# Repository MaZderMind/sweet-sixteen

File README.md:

# Sweet Sixteen
> a 16x2 Characters Sixten-Segment, RaspberryPi driven Display

## Quick Links
 * <a href="Hardware/Schematic.pdf">Schematic (PDF)</a>
 * <a href="Hardware/PCB-Layout.png">PCB Layout (Image)</a>
 * <a href="Hardware/BOM.ods">BOM</a>
 * <a href="Datasheets/">Datasheets</a>
 * <a href="https://github.com/MaZderMind/sweet-sixteen-scheduler">Software</a>

## System Design

The System is built around [STP16CPC26](Datasheets/STP16CPC26.pdf) LED-Drivers in a direct drive configuration. Each LED-Driver has 16 Constant-Current sinks, each of which powers one Segment of the [PSA12-11](Datasheets/PSA12_11CGKWA.pdf) 16-Segment Displays.

The PCBs are built to be Chainable. The first Board in the Chain provides Data and the 5V Rail. It also carries the RaspberryPi "Piggy Back". The Board powers the Pi via its GPIO-Header, so there is no need to supply extra Power to the Pi (and you should not do that.)

## Signal Flow

The RaspberryPi generates Clock and Data via its Hardware-SPI Port (GPIO 10 & 11). Additionally it generates a Latch-Signal on GPIO 22 and an inverted Output-Enable Signal, which is can be used to Dim the LED-Drivers down, on one of its Hardware PWM Pins (GPIO 18).

All of these Signals are 3.3V rated. They are directly fed into a [SN74HCT08](Datasheets/sn74hct08.pdf) and-gate which is used to convert the Signals to 5V compatible swing. These Signal then go on a parallel bus to all LED-Drivers (Clock, Latch and Output-Enable) resp. to the first LED-Driver (Data).

The LED-Drivers behave like Shift-Registers on the Data-Side, so the Data-Line ist chained from the input of one LED-Driver to the next, through all 9 Drivers. Drivers 1-8 each control one of the 16 Segments of one of the 8 Digits, while the 9th Driver controls the Decimal Points of all Digits as well as the Row of the 8 LEDs on the bottom of the PCB.

The Data-Output of the last LED-Driver as well as the paralleld Bus of Clock, Latch and Output Enable are fed to another [SN74HCT08](Datasheets/sn74hct08.pdf) and-gate which is here used as a line-driver to drive the LED-Drivers on the next PCB. After the and-gate the Signal is routed to Solder-Pads on the edge of the PCB which line up with matching Pads on the opposite Edge of the next PCB.

The Signals coming from those Pads feed into the next 9 LED-Drivers, just as the Raspberry-Pi did on the first PCB. The Components needed to interface to the Raspberry-Pi (Connectors, Fuse, and-Gate and some Caps) are not fitted on the following PCBs.

## Power System

The Whole System is Powered from a Notebook-Plugpack. I chose a Dell 19V/90W Plugpack because they are quite easy to get new or used on ebay for a small amount of money everywhere on the world. I terms of Power per Euro/Dollar Notebook-Chargers are unbeatable.

The 19V (actually the Input-Rail can range from 15V to 40V DC) is fed into two DC-DC Converter Modules on the first PCB, each of which is capable of generating up to 3A.

The first DC-DC Converter generates 5V and powers the RaspberryPi as well as as all the Logic-ICs on all PCBs.
The second Converter generates a 4.4V rail used to Power the LEDs – but this time only on the first PCB.

The following PCBs accept the 5V VCC Rail generated on the first PCB as well as the input-voltage from the Plugpack, also via Pads on the Edge of the PCBs. They are only fitted with the second DC-DC Converter and generate their own 4.4V VLED Rail for their LEDS.

When all LEDs ar on, the System draws about 45W or a little more, so 60W Dell Charger should also be okay. Take a look at the [Power Calculations](Hardware/Power%20Calculations.ods) to learn how the Current is consumed and which Temperature-Rise is to expect from the LED-Drivers.

## Software

The Software that runs the Display, pulls down the latest tweets, shows what the canteen has for Lunch, Blinks when a Software-Build fails or when it's a colleagues birthday grows over on [MaZderMind/sweet-sixteen-scheduler](https://github.com/MaZderMind/sweet-sixteen-scheduler).

## Build one yourself

To build your own you need
 * some PCBs
 * some Parts
 * a RaspberryPi
 * time, patience and tools to solder the SMD-Components (which is totally doable by Hand vith a good soldering Iron)

For the PCBs you can use the [pre-generated Gerbers](Gerbers/) but *be aware* that these are the Gerbers for rev1. I fixed some Bugs in rev1 but my Display uses rev0 boards and I have *not ordered or testet* the rev1 PCBs, though I'm quite sure they will work. If you want to play save, you can Download the rev0 Gerbers from the [rev0 Release-Page](https://github.com/MaZderMind/sweet-sixteen/releases/tag/rev0).

On the other Hand you might want to design in another Power-Connector, if you don't want to use Dell Plugpacks. The Schematics and PCBs are made with [KiCad](http://kicad-pcb.org/) which is Free Software and available on all Operating Systems. For the Parts please take a look at the [BOM](Hardware/BOM.ods) which contains all Parts I used.

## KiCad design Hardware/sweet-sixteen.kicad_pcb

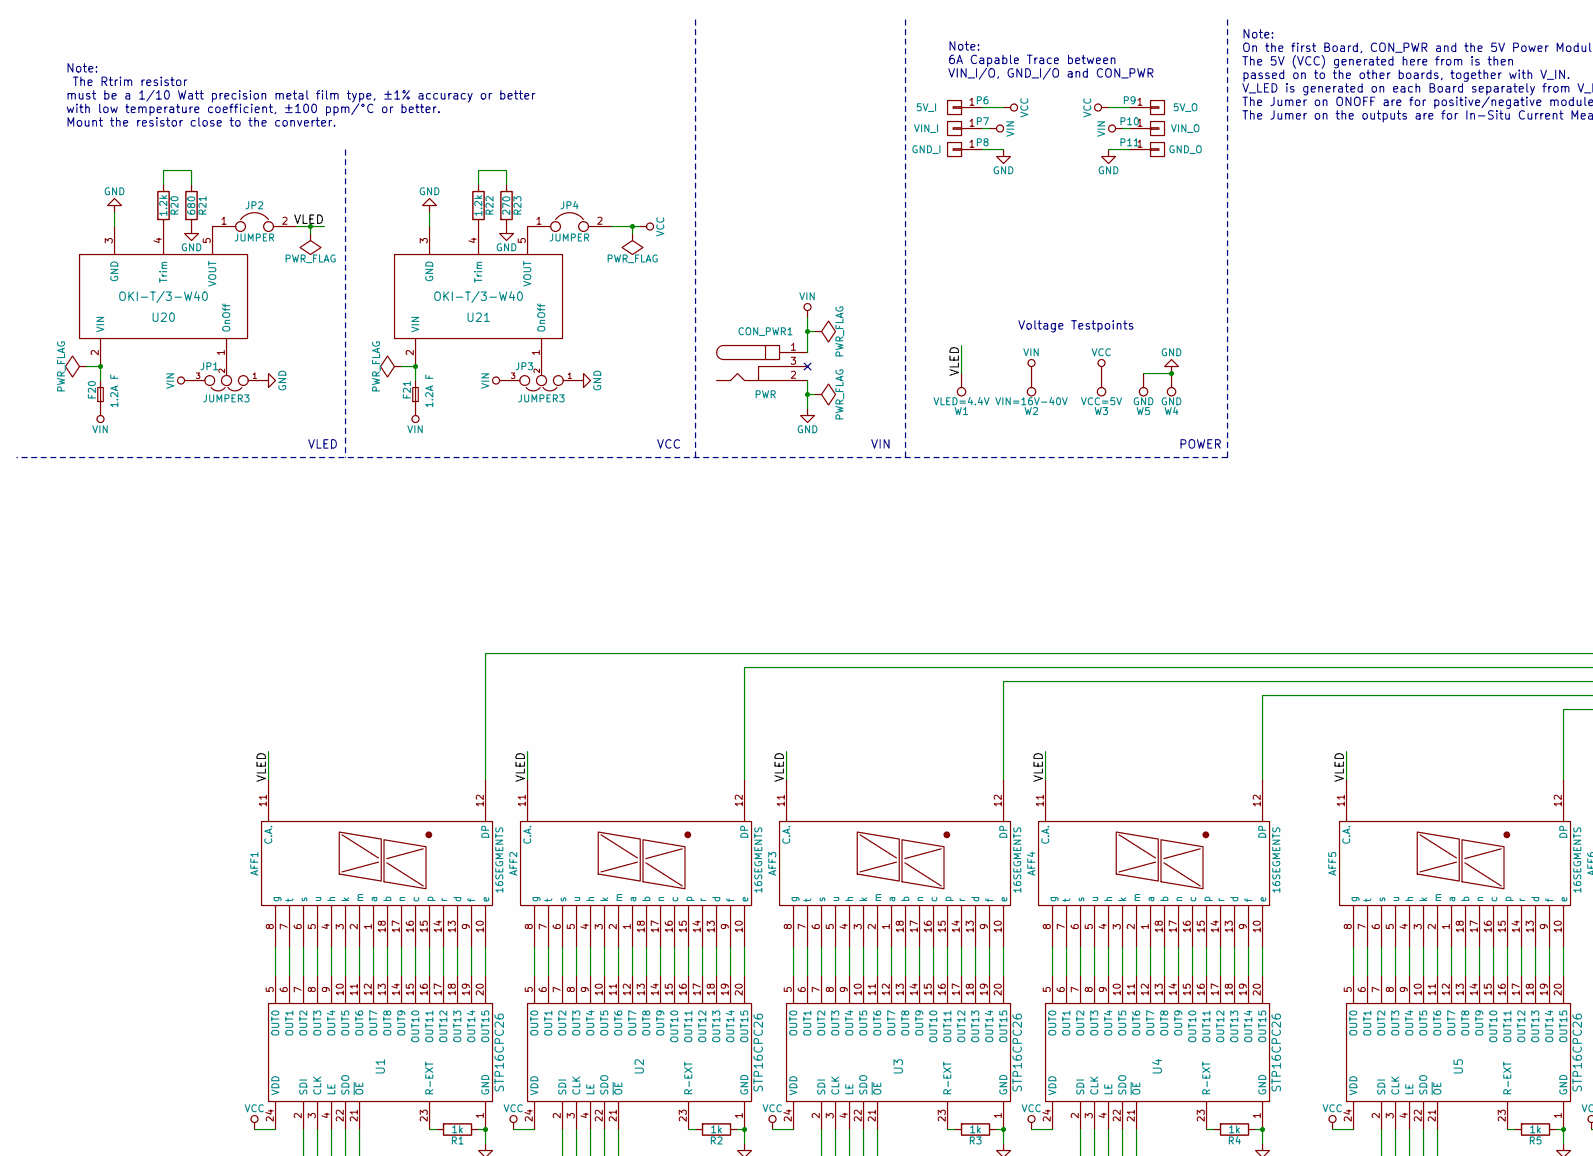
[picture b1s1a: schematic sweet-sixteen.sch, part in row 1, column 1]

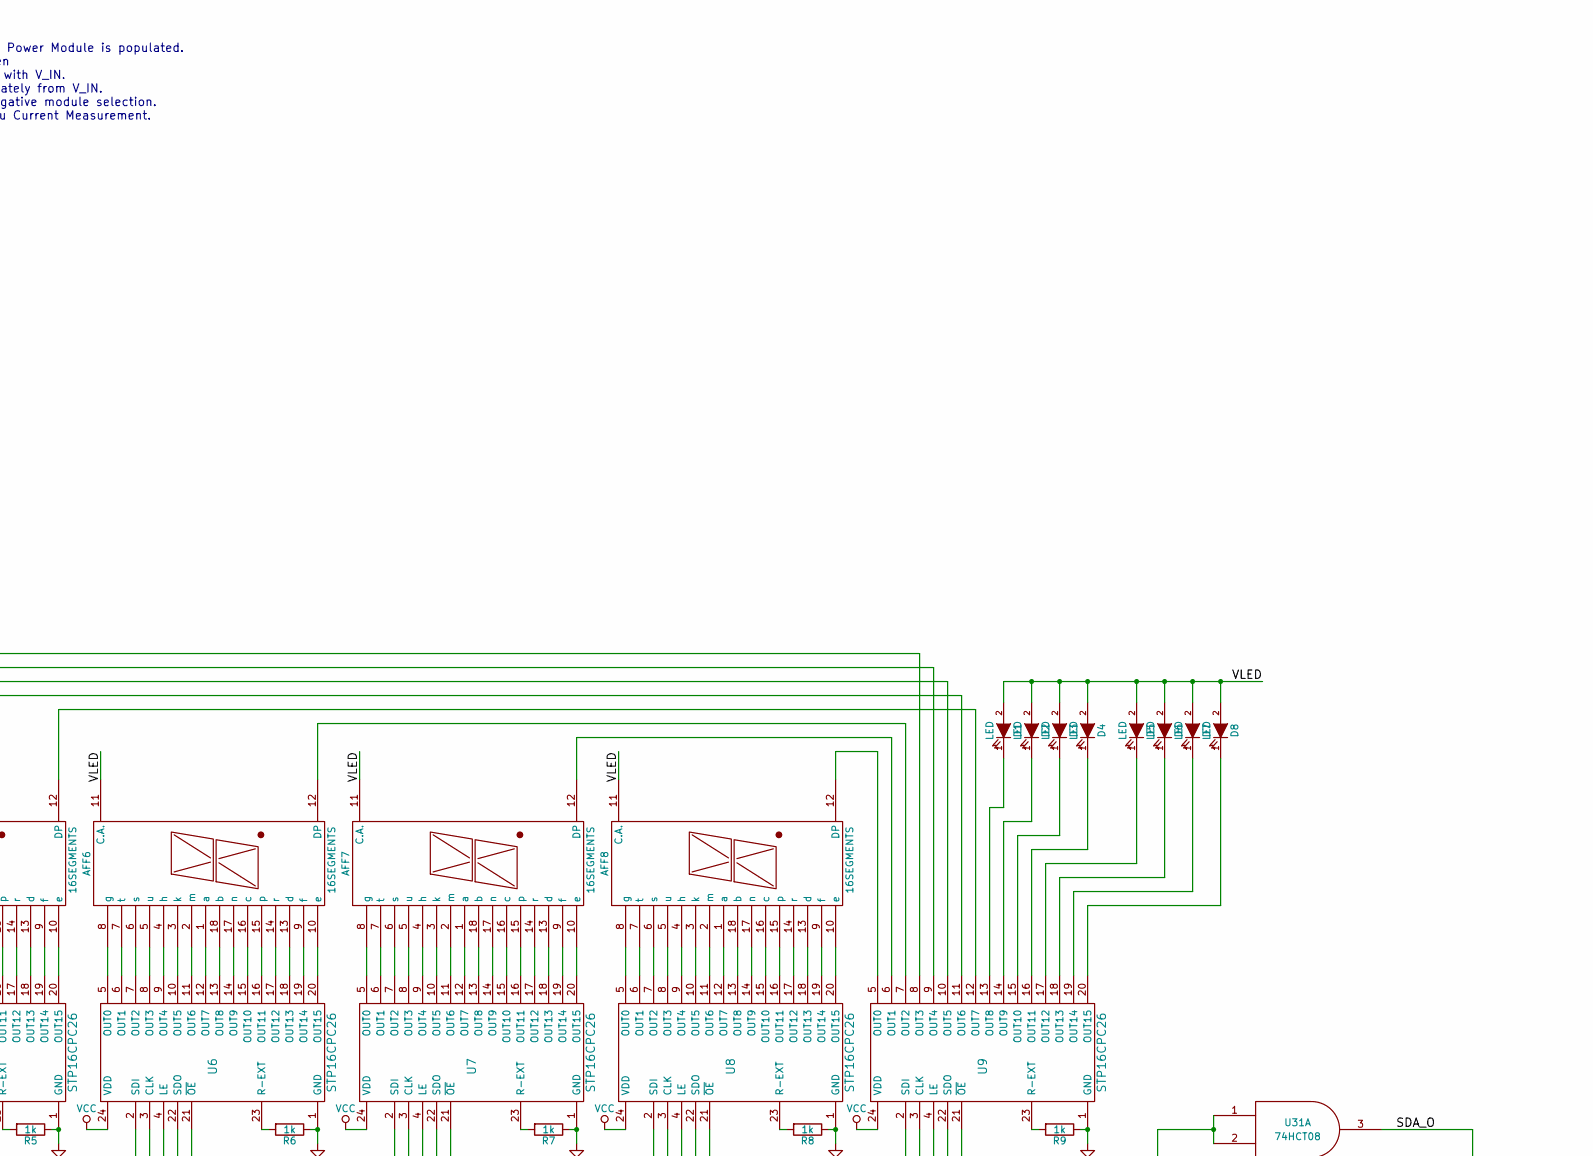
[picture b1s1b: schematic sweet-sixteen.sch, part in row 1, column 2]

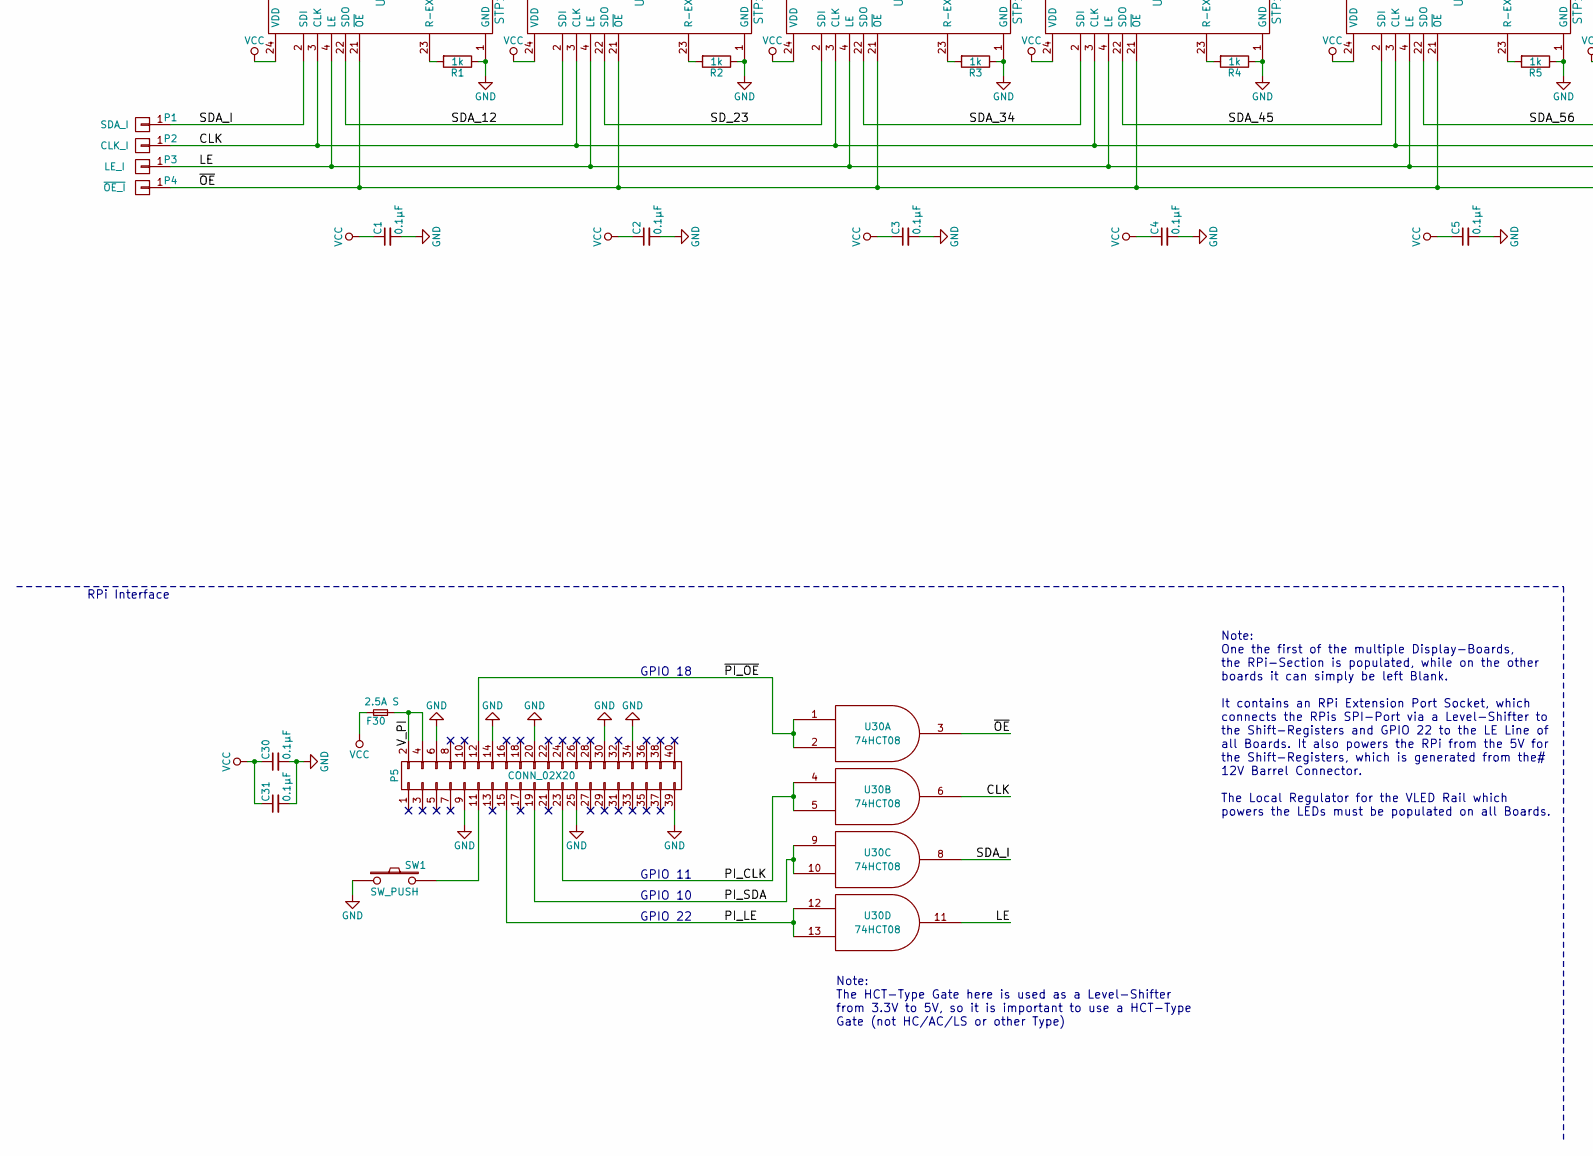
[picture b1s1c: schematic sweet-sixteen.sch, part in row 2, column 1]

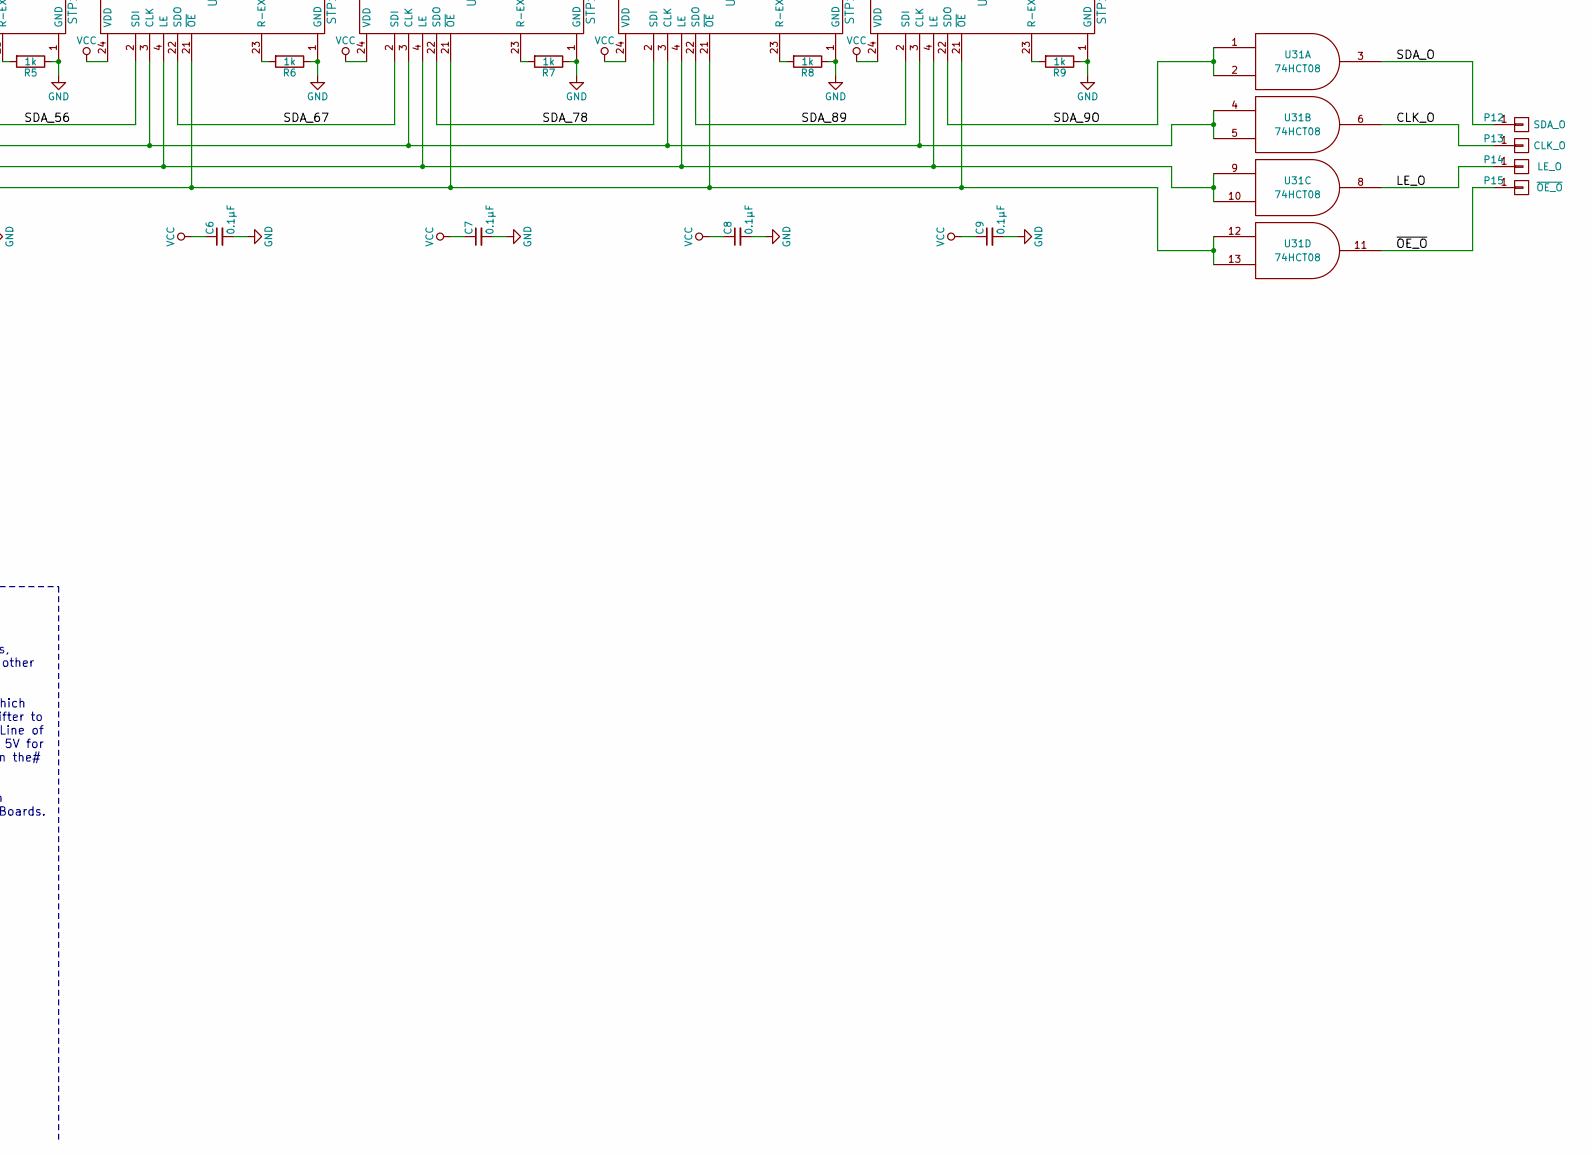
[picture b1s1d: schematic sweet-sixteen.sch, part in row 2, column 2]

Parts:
AFF1, AFF2, AFF3, AFF4, AFF5, AFF6, AFF7, AFF8: 16SEGMENTS; PSA12-11
C1, C2, C3, C4, C5, C6, C7, C8, C9, C30, C31: 0.1μF; C_0805_HandSoldering
CON_PWR1: PWR; DELL-PCON
D1, D2, D3, D4, D5, D6, D7, D8: LED; LED-5MM
F20, F21: 1.2A F; SMD-2112_Pol
F30: 2.5A S; SMD-2112_Pol
JP1, JP3: JUMPER3; SMD_Jumper_3
JP2, JP4: JUMPER; SMD_Jumper_2
P1: SDA_I; Measurement_Point_Square-SMD-Pad_Big
P2: CLK_I; Measurement_Point_Square-SMD-Pad_Big
P3: LE_I; Measurement_Point_Square-SMD-Pad_Big
P4: ~OE_I; Measurement_Point_Square-SMD-Pad_Big
P5: CONN_02X20; rpi-header
P6: 5V_I; Measurement_Point_Square-SMD-Pad_Big
P7: VIN_I; Measurement_Point_Square-SMD-Pad_Big
P8: GND_I; Measurement_Point_Square-SMD-Pad_Big
P9: 5V_O; Measurement_Point_Square-SMD-Pad_Big
P10: VIN_O; Measurement_Point_Square-SMD-Pad_Big
P11: GND_O; Measurement_Point_Square-SMD-Pad_Big
P12: SDA_O; Measurement_Point_Square-SMD-Pad_Big
P13: CLK_O; Measurement_Point_Square-SMD-Pad_Big
P14: LE_O; Measurement_Point_Square-SMD-Pad_Big
P15: ~OE_O; Measurement_Point_Square-SMD-Pad_Big
R1, R2, R3, R4, R5, R6, R7, R8, R9: 1k; R_1206_HandSoldering
R20, R22: 1.2k; R_1206_HandSoldering
R21: 680; R_1206_HandSoldering
R23: 270; R_1206_HandSoldering
SW1: SW_PUSH; ADTSM61
U1, U2, U3, U4, U5, U6, U7, U8, U9: STP16CPC26; STP16CPC26MTR
U20, U21: OKI-T/3-W40; OKI-T3
U30, U31: 74HCT08; SN74HCT08D
W1: VLED=4.4V; Measurement_Point_Round-SMD-Pad_Big
W2: VIN=16V-40V; Measurement_Point_Round-SMD-Pad_Big
W3: VCC=5V; Measurement_Point_Round-SMD-Pad_Big
W4, W5: GND; Measurement_Point_Round-SMD-Pad_Big

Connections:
/CLK: P2.1, U1.3 (CLK), U2.3 (CLK), U3.3 (CLK), U4.3 (CLK), U5.3 (CLK), U6.3 (CLK), U7.3 (CLK), U8.3 (CLK), U9.3 (CLK), U30.6, U31.4, U31.5
/CLK_O: P13.1, U31.6
/LE: P3.1, U1.4 (LE), U2.4 (LE), U3.4 (LE), U4.4 (LE), U5.4 (LE), U6.4 (LE), U7.4 (LE), U8.4 (LE), U9.4 (LE), U30.11, U31.9, U31.10
/LE_O: P14.1, U31.8
/PI_CLK: P5.23, U30.4, U30.5
/PI_LE: P5.15, U30.12, U30.13
/PI_SDA: P5.19, U30.9, U30.10
/SDA_9O: U9.22 (SDO), U31.1, U31.2
/SDA_12: U1.22 (SDO), U2.2 (SDI)
/SDA_34: U3.22 (SDO), U4.2 (SDI)
/SDA_45: U4.22 (SDO), U5.2 (SDI)
/SDA_56: U5.22 (SDO), U6.2 (SDI)
/SDA_67: U6.22 (SDO), U7.2 (SDI)
/SDA_78: U7.22 (SDO), U8.2 (SDI)
/SDA_89: U8.22 (SDO), U9.2 (SDI)
/SDA_I: P1.1, U1.2 (SDI), U30.8
/SDA_O: P12.1, U31.3
/SD_23: U2.22 (SDO), U3.2 (SDI)
/VLED: AFF1.11 (C.A.), AFF2.11 (C.A.), AFF3.11 (C.A.), AFF4.11 (C.A.), AFF5.11 (C.A.), AFF6.11 (C.A.), AFF7.11 (C.A.), AFF8.11 (C.A.), D1.2 (A), D2.2 (A), D3.2 (A), D4.2 (A), D5.2 (A), D6.2 (A), D7.2 (A), D8.2 (A), JP2.2, W1.1
/V_PI: F30.1, P5.2, P5.4
/~OE: P4.1, U1.21 (~OE), U2.21 (~OE), U3.21 (~OE), U4.21 (~OE), U5.21 (~OE), U6.21 (~OE), U7.21 (~OE), U8.21 (~OE), U9.21 (~OE), U30.3, U31.12, U31.13
/~OE_O: P15.1, U31.11
/~PI_OE: P5.12, U30.1, U30.2
GND: C1.2, C2.2, C3.2, C4.2, C5.2, C6.2, C7.2, C8.2, C9.2, C30.2, C31.2, CON_PWR1.2, JP1.1, JP3.1, P5.6, P5.9, P5.14, P5.20, P5.25, P5.30, P5.34, P5.39, P8.1, P11.1, R1.1, R2.1, R3.1, R4.1, R5.1, R6.1, R7.1, R8.1, R9.1, R21.2, R23.2, SW1.1, U1.1 (GND), U2.1 (GND), U3.1 (GND), U4.1 (GND), U5.1 (GND), U6.1 (GND), U7.1 (GND), U8.1 (GND), U9.1 (GND), U20.3 (GND), U21.3 (GND), U30.7 (GND), U31.7 (GND), W4.1, W5.1
unnamed: AFF1.1 (a), U1.12 (OUT7)
unnamed: AFF1.2 (m), U1.11 (OUT6)
unnamed: AFF1.3 (k), U1.10 (OUT5)
unnamed: AFF1.4 (h), U1.9 (OUT4)
unnamed: AFF1.5 (u), U1.8 (OUT3)
unnamed: AFF1.6 (s), U1.7 (OUT2)
unnamed: AFF1.7 (t), U1.6 (OUT1)
unnamed: AFF1.8 (g), U1.5 (OUT0)
unnamed: AFF1.9 (f), U1.19 (OUT14)
unnamed: AFF1.10 (e), U1.20 (OUT15)
unnamed: AFF1.12 (DP), U9.8 (OUT3)
unnamed: AFF1.13 (d), U1.18 (OUT13)
unnamed: AFF1.14 (r), U1.17 (OUT12)
unnamed: AFF1.15 (p), U1.16 (OUT11)
unnamed: AFF1.16 (c), U1.15 (OUT10)
unnamed: AFF1.17 (n), U1.14 (OUT9)
unnamed: AFF1.18 (b), U1.13 (OUT8)
unnamed: AFF2.1 (a), U2.12 (OUT7)
unnamed: AFF2.2 (m), U2.11 (OUT6)
unnamed: AFF2.3 (k), U2.10 (OUT5)
unnamed: AFF2.4 (h), U2.9 (OUT4)
unnamed: AFF2.5 (u), U2.8 (OUT3)
unnamed: AFF2.6 (s), U2.7 (OUT2)
unnamed: AFF2.7 (t), U2.6 (OUT1)
unnamed: AFF2.8 (g), U2.5 (OUT0)
unnamed: AFF2.9 (f), U2.19 (OUT14)
unnamed: AFF2.10 (e), U2.20 (OUT15)
unnamed: AFF2.12 (DP), U9.9 (OUT4)
unnamed: AFF2.13 (d), U2.18 (OUT13)
unnamed: AFF2.14 (r), U2.17 (OUT12)
unnamed: AFF2.15 (p), U2.16 (OUT11)
unnamed: AFF2.16 (c), U2.15 (OUT10)
unnamed: AFF2.17 (n), U2.14 (OUT9)
unnamed: AFF2.18 (b), U2.13 (OUT8)
unnamed: AFF3.1 (a), U3.12 (OUT7)
unnamed: AFF3.2 (m), U3.11 (OUT6)
unnamed: AFF3.3 (k), U3.10 (OUT5)
unnamed: AFF3.4 (h), U3.9 (OUT4)
unnamed: AFF3.5 (u), U3.8 (OUT3)
unnamed: AFF3.6 (s), U3.7 (OUT2)
unnamed: AFF3.7 (t), U3.6 (OUT1)
unnamed: AFF3.8 (g), U3.5 (OUT0)
unnamed: AFF3.9 (f), U3.19 (OUT14)
unnamed: AFF3.10 (e), U3.20 (OUT15)
unnamed: AFF3.12 (DP), U9.10 (OUT5)
unnamed: AFF3.13 (d), U3.18 (OUT13)
unnamed: AFF3.14 (r), U3.17 (OUT12)
unnamed: AFF3.15 (p), U3.16 (OUT11)
unnamed: AFF3.16 (c), U3.15 (OUT10)
unnamed: AFF3.17 (n), U3.14 (OUT9)
unnamed: AFF3.18 (b), U3.13 (OUT8)
unnamed: AFF4.1 (a), U4.12 (OUT7)
unnamed: AFF4.2 (m), U4.11 (OUT6)
unnamed: AFF4.3 (k), U4.10 (OUT5)
unnamed: AFF4.4 (h), U4.9 (OUT4)
unnamed: AFF4.5 (u), U4.8 (OUT3)
unnamed: AFF4.6 (s), U4.7 (OUT2)
unnamed: AFF4.7 (t), U4.6 (OUT1)
unnamed: AFF4.8 (g), U4.5 (OUT0)
unnamed: AFF4.9 (f), U4.19 (OUT14)
unnamed: AFF4.10 (e), U4.20 (OUT15)
unnamed: AFF4.12 (DP), U9.11 (OUT6)
unnamed: AFF4.13 (d), U4.18 (OUT13)
unnamed: AFF4.14 (r), U4.17 (OUT12)
unnamed: AFF4.15 (p), U4.16 (OUT11)
unnamed: AFF4.16 (c), U4.15 (OUT10)
unnamed: AFF4.17 (n), U4.14 (OUT9)
unnamed: AFF4.18 (b), U4.13 (OUT8)
unnamed: AFF5.1 (a), U5.12 (OUT7)
unnamed: AFF5.2 (m), U5.11 (OUT6)
unnamed: AFF5.3 (k), U5.10 (OUT5)
unnamed: AFF5.4 (h), U5.9 (OUT4)
unnamed: AFF5.5 (u), U5.8 (OUT3)
unnamed: AFF5.6 (s), U5.7 (OUT2)
unnamed: AFF5.7 (t), U5.6 (OUT1)
unnamed: AFF5.8 (g), U5.5 (OUT0)
unnamed: AFF5.9 (f), U5.19 (OUT14)
unnamed: AFF5.10 (e), U5.20 (OUT15)
unnamed: AFF5.12 (DP), U9.12 (OUT7)
unnamed: AFF5.13 (d), U5.18 (OUT13)
unnamed: AFF5.14 (r), U5.17 (OUT12)
unnamed: AFF5.15 (p), U5.16 (OUT11)
unnamed: AFF5.16 (c), U5.15 (OUT10)
unnamed: AFF5.17 (n), U5.14 (OUT9)
unnamed: AFF5.18 (b), U5.13 (OUT8)
unnamed: AFF6.1 (a), U6.12 (OUT7)
unnamed: AFF6.2 (m), U6.11 (OUT6)
unnamed: AFF6.3 (k), U6.10 (OUT5)
unnamed: AFF6.4 (h), U6.9 (OUT4)
unnamed: AFF6.5 (u), U6.8 (OUT3)
unnamed: AFF6.6 (s), U6.7 (OUT2)
unnamed: AFF6.7 (t), U6.6 (OUT1)
unnamed: AFF6.8 (g), U6.5 (OUT0)
unnamed: AFF6.9 (f), U6.19 (OUT14)
unnamed: AFF6.10 (e), U6.20 (OUT15)
unnamed: AFF6.12 (DP), U9.7 (OUT2)
unnamed: AFF6.13 (d), U6.18 (OUT13)
unnamed: AFF6.14 (r), U6.17 (OUT12)
unnamed: AFF6.15 (p), U6.16 (OUT11)
unnamed: AFF6.16 (c), U6.15 (OUT10)
unnamed: AFF6.17 (n), U6.14 (OUT9)
unnamed: AFF6.18 (b), U6.13 (OUT8)
unnamed: AFF7.1 (a), U7.12 (OUT7)
unnamed: AFF7.2 (m), U7.11 (OUT6)
unnamed: AFF7.3 (k), U7.10 (OUT5)
unnamed: AFF7.4 (h), U7.9 (OUT4)
unnamed: AFF7.5 (u), U7.8 (OUT3)
unnamed: AFF7.6 (s), U7.7 (OUT2)
unnamed: AFF7.7 (t), U7.6 (OUT1)
unnamed: AFF7.8 (g), U7.5 (OUT0)
unnamed: AFF7.9 (f), U7.19 (OUT14)
unnamed: AFF7.10 (e), U7.20 (OUT15)
unnamed: AFF7.12 (DP), U9.6 (OUT1)
unnamed: AFF7.13 (d), U7.18 (OUT13)
unnamed: AFF7.14 (r), U7.17 (OUT12)
unnamed: AFF7.15 (p), U7.16 (OUT11)
unnamed: AFF7.16 (c), U7.15 (OUT10)
unnamed: AFF7.17 (n), U7.14 (OUT9)
unnamed: AFF7.18 (b), U7.13 (OUT8)
unnamed: AFF8.1 (a), U8.12 (OUT7)
unnamed: AFF8.2 (m), U8.11 (OUT6)
unnamed: AFF8.3 (k), U8.10 (OUT5)
unnamed: AFF8.4 (h), U8.9 (OUT4)
unnamed: AFF8.5 (u), U8.8 (OUT3)
unnamed: AFF8.6 (s), U8.7 (OUT2)
unnamed: AFF8.7 (t), U8.6 (OUT1)
unnamed: AFF8.8 (g), U8.5 (OUT0)
unnamed: AFF8.9 (f), U8.19 (OUT14)
unnamed: AFF8.10 (e), U8.20 (OUT15)
unnamed: AFF8.12 (DP), U9.5 (OUT0)
unnamed: AFF8.13 (d), U8.18 (OUT13)
unnamed: AFF8.14 (r), U8.17 (OUT12)
unnamed: AFF8.15 (p), U8.16 (OUT11)
unnamed: AFF8.16 (c), U8.15 (OUT10)
unnamed: AFF8.17 (n), U8.14 (OUT9)
unnamed: AFF8.18 (b), U8.13 (OUT8)
unnamed: D1.1 (K), U9.13 (OUT8)
unnamed: D2.1 (K), U9.14 (OUT9)
unnamed: D3.1 (K), U9.15 (OUT10)
unnamed: D4.1 (K), U9.16 (OUT11)
unnamed: D5.1 (K), U9.17 (OUT12)
unnamed: D6.1 (K), U9.18 (OUT13)
unnamed: D7.1 (K), U9.19 (OUT14)
unnamed: D8.1 (K), U9.20 (OUT15)
unnamed: F20.2, U20.2 (VIN)
unnamed: F21.2, U21.2 (VIN)
unnamed: JP1.2, U20.1 (OnOff)
unnamed: JP2.1, U20.5 (VOUT)
unnamed: JP3.2, U21.1 (OnOff)
unnamed: JP4.1, U21.5 (VOUT)
unnamed: P5.11, SW1.2
unnamed: R1.2, U1.23 (R-EXT)
unnamed: R2.2, U2.23 (R-EXT)
unnamed: R3.2, U3.23 (R-EXT)
unnamed: R4.2, U4.23 (R-EXT)
unnamed: R5.2, U5.23 (R-EXT)
unnamed: R6.2, U6.23 (R-EXT)
unnamed: R7.2, U7.23 (R-EXT)
unnamed: R8.2, U8.23 (R-EXT)
unnamed: R9.2, U9.23 (R-EXT)
unnamed: R20.1, R21.1
unnamed: R20.2, U20.4 (Trim)
unnamed: R22.1, R23.1
unnamed: R22.2, U21.4 (Trim)
VCC: C1.1, C2.1, C3.1, C4.1, C5.1, C6.1, C7.1, C8.1, C9.1, C30.1, C31.1, F30.2, JP4.2, P6.1, P9.1, U1.24 (VDD), U2.24 (VDD), U3.24 (VDD), U4.24 (VDD), U5.24 (VDD), U6.24 (VDD), U7.24 (VDD), U8.24 (VDD), U9.24 (VDD), U30.14 (VCC), U31.14 (VCC), W3.1
VIN: CON_PWR1.1, F20.1, F21.1, JP1.3, JP3.3, P7.1, P10.1, W2.1

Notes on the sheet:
RPi Interface
Note: 6A Capable Trace between VIN_I/O, GND_I/O and CON_PWR
POWER
Note: One the first of the multiple Display-Boards, the RPi-Section is populated, while on the other boards it can simply be left Blank. It contains an RPi Extension Port Socket, which connects the RPis SPI-Port via a Level-Shifter to the Shift-Registers and GPIO 22 to the LE Line of all Boards. It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
Note: On the first Board, CON_PWR and the 5V Power Module is populated. The 5V (VCC) generated here from is then passed on to the other boards, together with V_IN. V_LED is generated on each Board separately from V_IN. The Jumer on ONOFF are for positive/negative module selection. The Jumer on the 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
Voltage Testpoints
Note: The HCT-Type Gate here is used as a Level-Shifter from 3.3V to 5V, so it is important to use a HCT-Type Gate (not HC/AC/LS or other Type)
VCC
VLED
VIN
Note: The Rtrim resistor must be a 1/10 Watt precision metal film type, ±1% accuracy or better with low temperature coefficient, ±100 ppm/°C or better. Mount the resistor close to the converter.
GPIO 22
GPIO 18
GPIO 10
GPIO 11

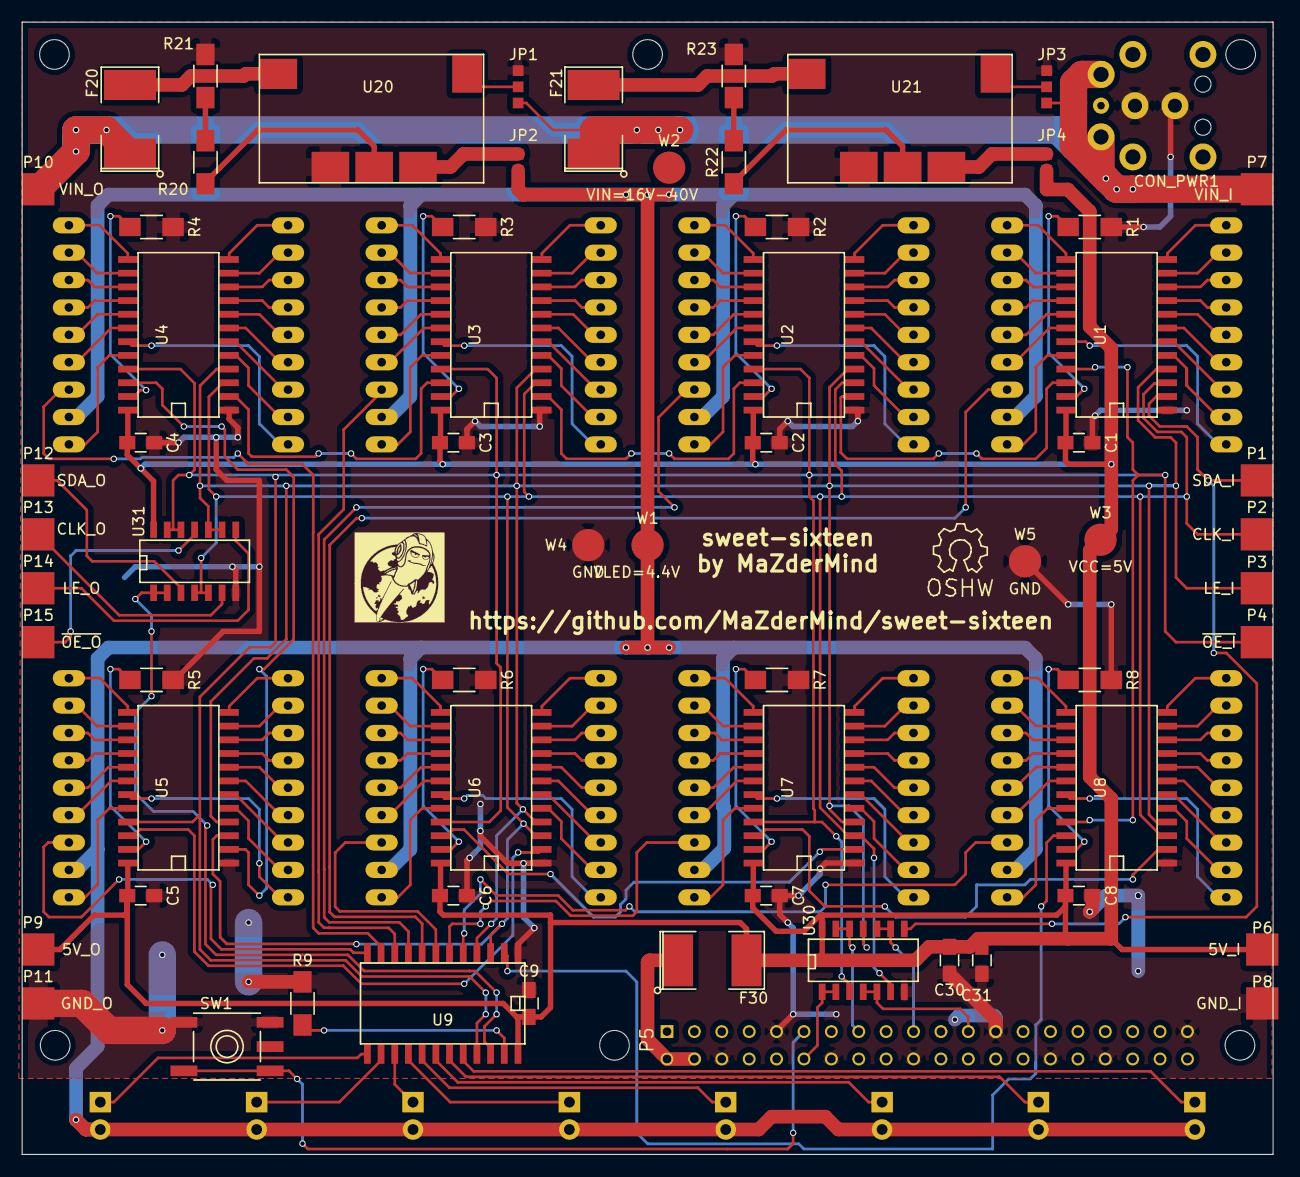
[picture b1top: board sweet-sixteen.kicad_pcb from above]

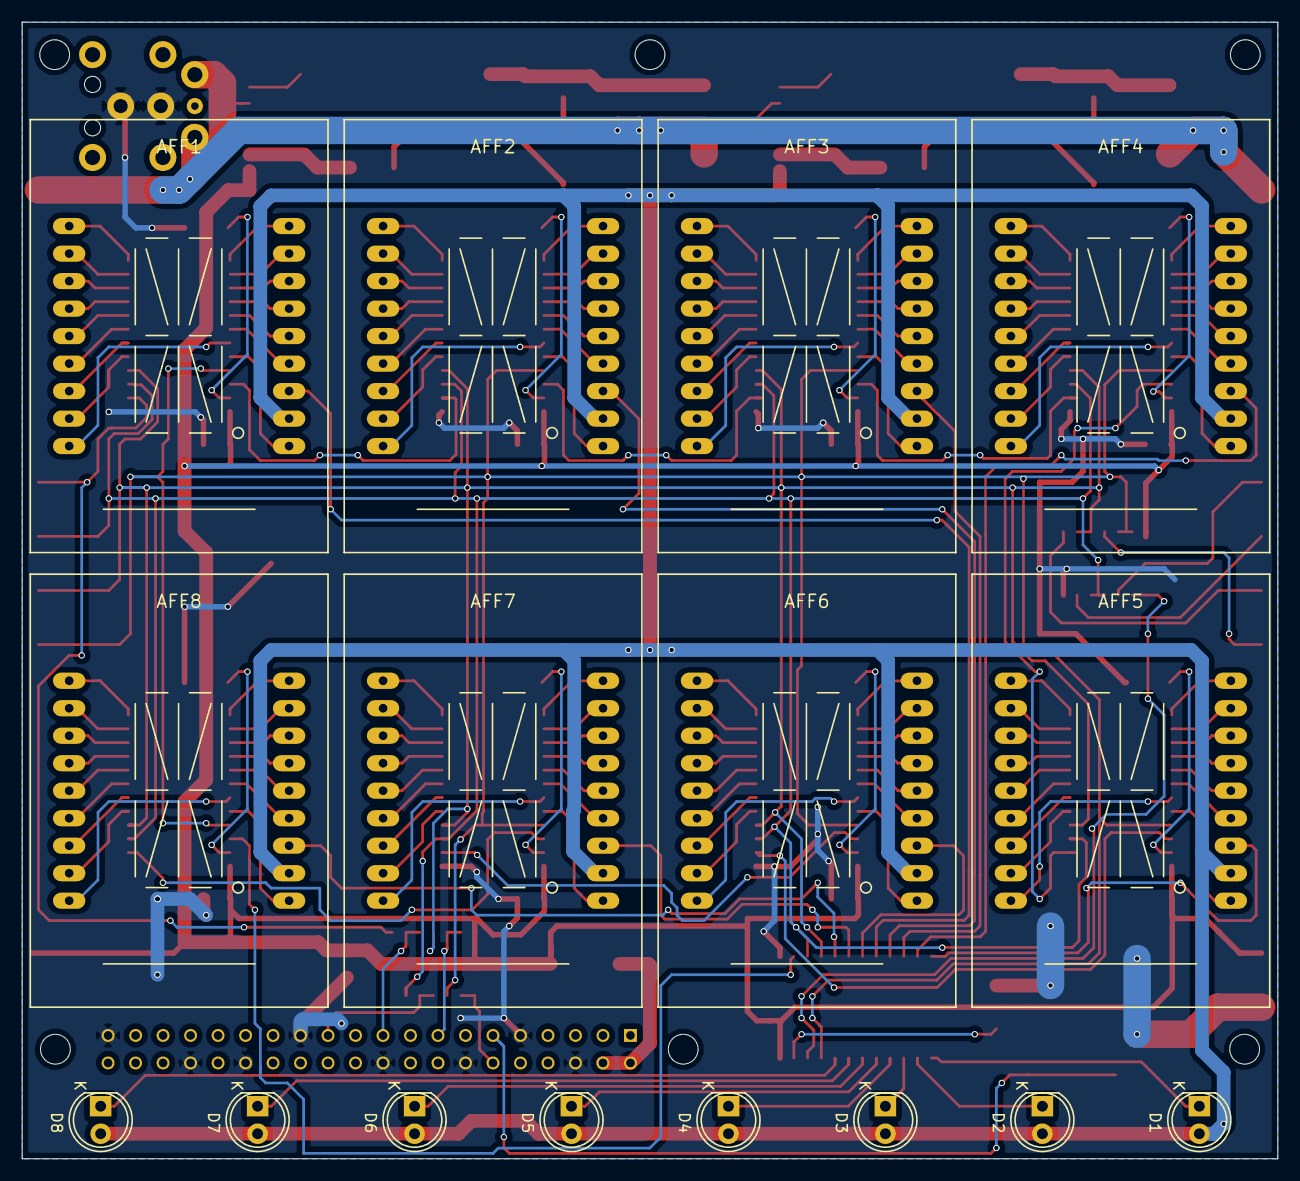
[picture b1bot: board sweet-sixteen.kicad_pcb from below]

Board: 2 copper layers, 116.0 x 105.0 mm, 82 parts (16 on the bottom side), 190 nets.

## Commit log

2016-12-10 empty project
2016-12-11 add datasheetds for displays
2016-12-11 add digits to lib
2016-12-11 add datasheet for LED-DRiver
2016-12-11 add BOM csv
2016-12-11 ignore LobreOFfice Lockfile
2016-12-11 place LED Modules
2016-12-11 add led-drivers to schematic
2016-12-11 wire up displays and driver
2016-12-11 add power & gnd
2016-12-11 restructute sch to be in line, add bus and i/o connector pads
2016-12-11 add power in, pi note and pi interface
2016-12-13 add level shifter, power net, 9th driver
2016-12-13 make more use of unused space
2016-12-13 make even more use out of that unused space
2017-02-19 update docs
2017-02-19 remote control test-sw and updated power calc
2017-02-19 redo schematic layout, pi interface, add output line driver, connect oe
2017-02-19 redo power section, make erc pass
2017-02-19 update bom, add 74hct08 datasheet
2017-02-19 update r value for trimming the vcc converter
2017-02-19 setup footprints for jumper and assign known footprints
2017-02-20 add note about Rtrim placement
2017-02-20 move things around
2017-02-20 basic pcb placement
2017-02-20 flip displays correctly and fix silkscreen layer
2017-02-20 remove 3d model from solder-jumper
2017-02-21 (remove) mounting hole text, move mounting holes
2017-02-21 add more gnd-testpoints, move testpoint-labels to silkscreen
2017-02-21 move labels
2017-03-03 redo pcb, footprints, pi interface
2017-03-03 soldermask fixup
2017-03-03 move footprints to inch locations, fix outline, lock footprints
2017-03-03 power tracks and via stitching
2017-03-03 flip display 1-4 for bwtter routability
2017-03-03 digital bus
2017-03-03 VLED 50 mils
2017-03-03 More Power traces
2017-03-04 rework some parts of the power network on the way fo implement the digital bus
2017-03-04 finished digital and analog net, vled and vcc
2017-03-04 route put DP net
2017-03-04 all done but GND
2017-03-04 finished gnd routing
2017-03-04 symbols & markings
2017-03-04 move pcb on paper
2017-03-04 image shots
2017-03-04 gerber files
2017-03-04 missing image symbols
2017-03-04 after gerber generation
2017-03-04 fix pi-power routing
2017-03-05 add 3d models
2017-03-05 change footprint to fit reality - *doh*
2017-03-05 move chaining-pads to new outline, position pcb in a well described location on paper, fix outline to be on mm boundaries
2017-03-05 reposition everything, rip up everything… meeeh…
2017-03-05 re-route things with more care
2017-03-05 re-route all
2017-03-05 move hardware to folder
2017-03-05 readme
2017-03-05 gerbers & drill-file
2017-03-05 add chained image
2017-03-08 use relative paths for 3d models
2017-03-08 add extra vias on VIN
2017-03-08 remove wrong gnd pin on pi connecor, add some labels
2017-03-08 add 2.5M mounting holes to the top of the pcb
2017-03-11 clean up BOM, add Button
2017-03-12 DELL Power Con
2017-03-19 place new connector footprint, update gerbers with soldermask
2017-05-12 Add fuses, make Parametric to number of Boards, Add Plugpack
2017-05-12 Cleanup Renderings
2017-05-12 Remove Test-Sketches, will be replaced by RPi Driver-Software
2017-05-12 licence file
2017-05-12 Documentation, Images and 3D Renderings
2017-05-12 move files around to make them easier to find
2017-05-12 rev1 changes
2017-05-12 add png/pdf version of schematic & pcb layout & link them from readme
